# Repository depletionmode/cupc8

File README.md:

## CUPC/8

###### Documentation
https://github.com/depletionmode/cupc8/blob/master/doc/CUPC8%20Manual.md

###### Blog
http://depletionmode.com/

### Terminal debugger

Build the debugger from `tools/` with:

```sh
nim c -d:release simtui.nim
```

Then run `kernel/debug.sh`. The guest display is embedded by default; use
`kernel/debug.sh --display:window` for the standalone SDL window. Terminal
graphics and color treatment can be selected explicitly:

```sh
kernel/debug.sh --gfx:half --theme:light
kernel/debug.sh --gfx:auto --theme:dark
```

Inside the debugger, `:display embedded|window`, `:theme auto|dark|light`, and
`:gfx auto|kitty|half` switch these modes without restarting. Pane borders can
be dragged with the mouse to resize the layout. Press `?` for the complete
keymap and command reference.

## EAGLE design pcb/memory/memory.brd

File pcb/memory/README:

Build:
$ avr-gcc xmega.c -mmcu=atxmega16a4 -o xmega.elf
$ avr-objcopy -O ihex xmega.elf xmega.hex

Flash:
* Patched avrdude for PDI
* avrdude.conf with id for x16c4
$ avrdude -C avrdude.conf -c usbasp -p x16c4 -U flash:w:xmega.hex:i -E noreset

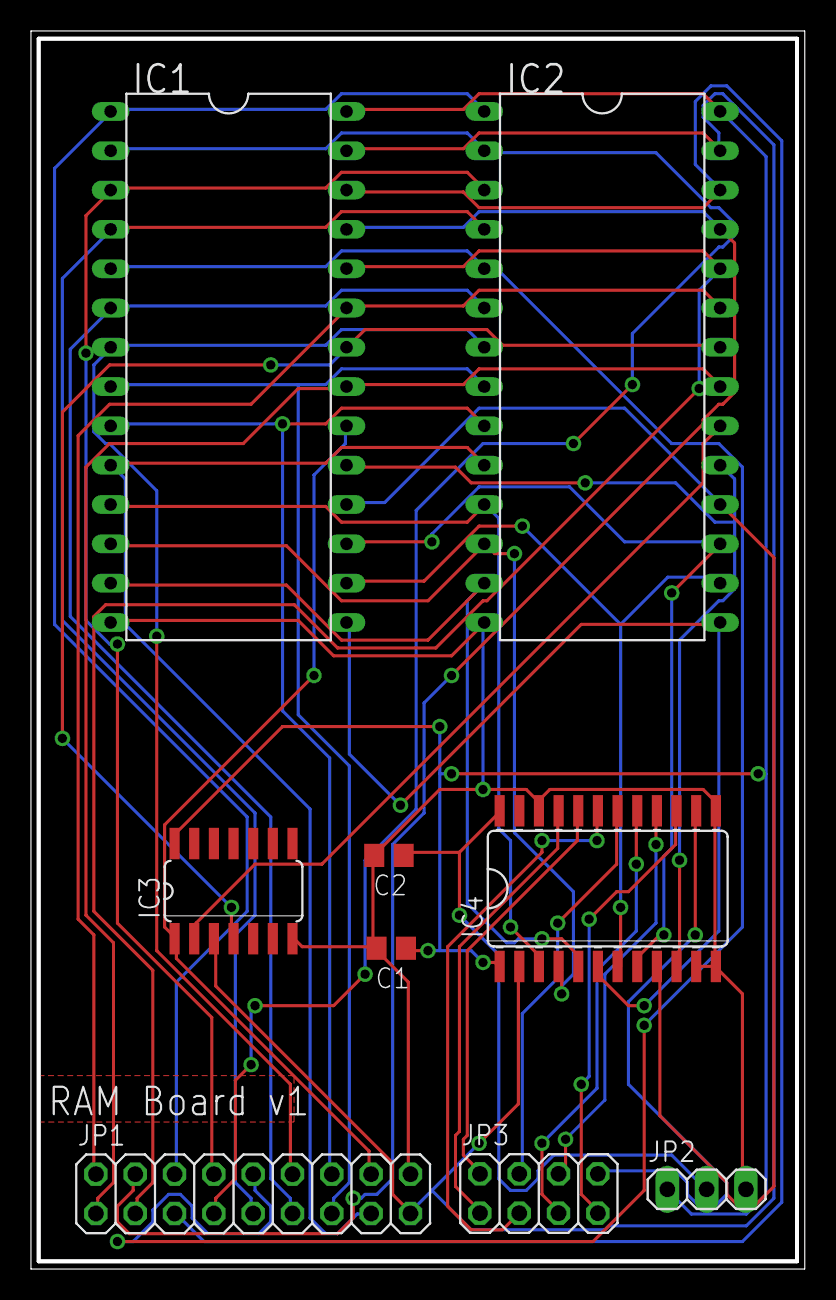
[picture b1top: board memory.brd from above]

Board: 2 copper layers, 50.0 x 80.0 mm, 9 parts (0 on the bottom side), 38 nets.

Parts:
C1, C2: 100nF; C0805
IC1, IC2: CY62256LL-PXC; DIL28-6
IC3: 74HC04D; SO14
IC4: 74LCC4245A; SO24W
JP1: 2X09
JP2: PWR; 1X03
JP3: 2X04

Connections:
!OE!: IC1.22, IC2.22, IC3.4
!WE!: IC1.27, IC2.27, IC3.3, IC4.2, JP1.17
+3V3: C2.1, IC4.24, JP2.2
+5V: C1.1, IC1.28, IC2.28, IC3.14, IC4.1, JP2.1
A0: IC1.21, IC2.21, JP1.1
A1: IC1.23, IC2.23, JP1.2
A2: IC1.24, IC2.24, JP1.3
A3: IC1.25, IC2.25, JP1.4
A4: IC1.26, IC2.26, JP1.5
A5: IC1.1, IC2.1, JP1.6
A6: IC1.2, IC2.2, JP1.7
A7: IC1.3, IC2.3, JP1.8
A8: IC1.4, IC2.4, JP1.9
A9: IC1.5, IC2.5, JP1.10
A10: IC1.6, IC2.6, JP1.11
A11: IC1.7, IC2.7, JP1.12
A12: IC1.8, IC2.8, JP1.13
A13: IC1.9, IC2.9, JP1.14
A14: IC1.10, IC2.10, JP1.15
A15: IC1.20, IC3.1, JP1.16
B0: IC1.11, IC2.11, IC4.3
B1: IC1.12, IC2.12, IC4.4
B2: IC1.13, IC2.13, IC4.5
B3: IC1.15, IC2.15, IC4.6
B4: IC1.16, IC2.16, IC4.7
B5: IC1.17, IC2.17, IC4.8
B6: IC1.18, IC2.18, IC4.9
B7: IC1.19, IC2.19, IC4.10
D0: IC4.21, JP3.1
D1: IC4.20, JP3.2
D2: IC4.19, JP3.3
D3: IC4.18, JP3.4
D4: IC4.17, JP3.5
D5: IC4.16, JP3.6
D6: IC4.15, JP3.7
D7: IC4.14, JP3.8
GND: C1.2, C2.2, IC1.14, IC2.14, IC3.7, IC4.11, IC4.12, IC4.13, IC4.22, JP1.18, JP2.3
unnamed: IC2.20, IC3.2
